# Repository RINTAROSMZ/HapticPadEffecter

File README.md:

# HapticPadEffecter
触感再現技術による音響効果フィードバックを備えたトラックパッド式エフェクター

Capative PCB trackpad (diamond pattern)

Intuitive manipulation of the parameters of Distortion and Spatial effects

Touch IC:MTCH6102

Haptic:DRV2605L+LRA

DigiPot:MCP42010

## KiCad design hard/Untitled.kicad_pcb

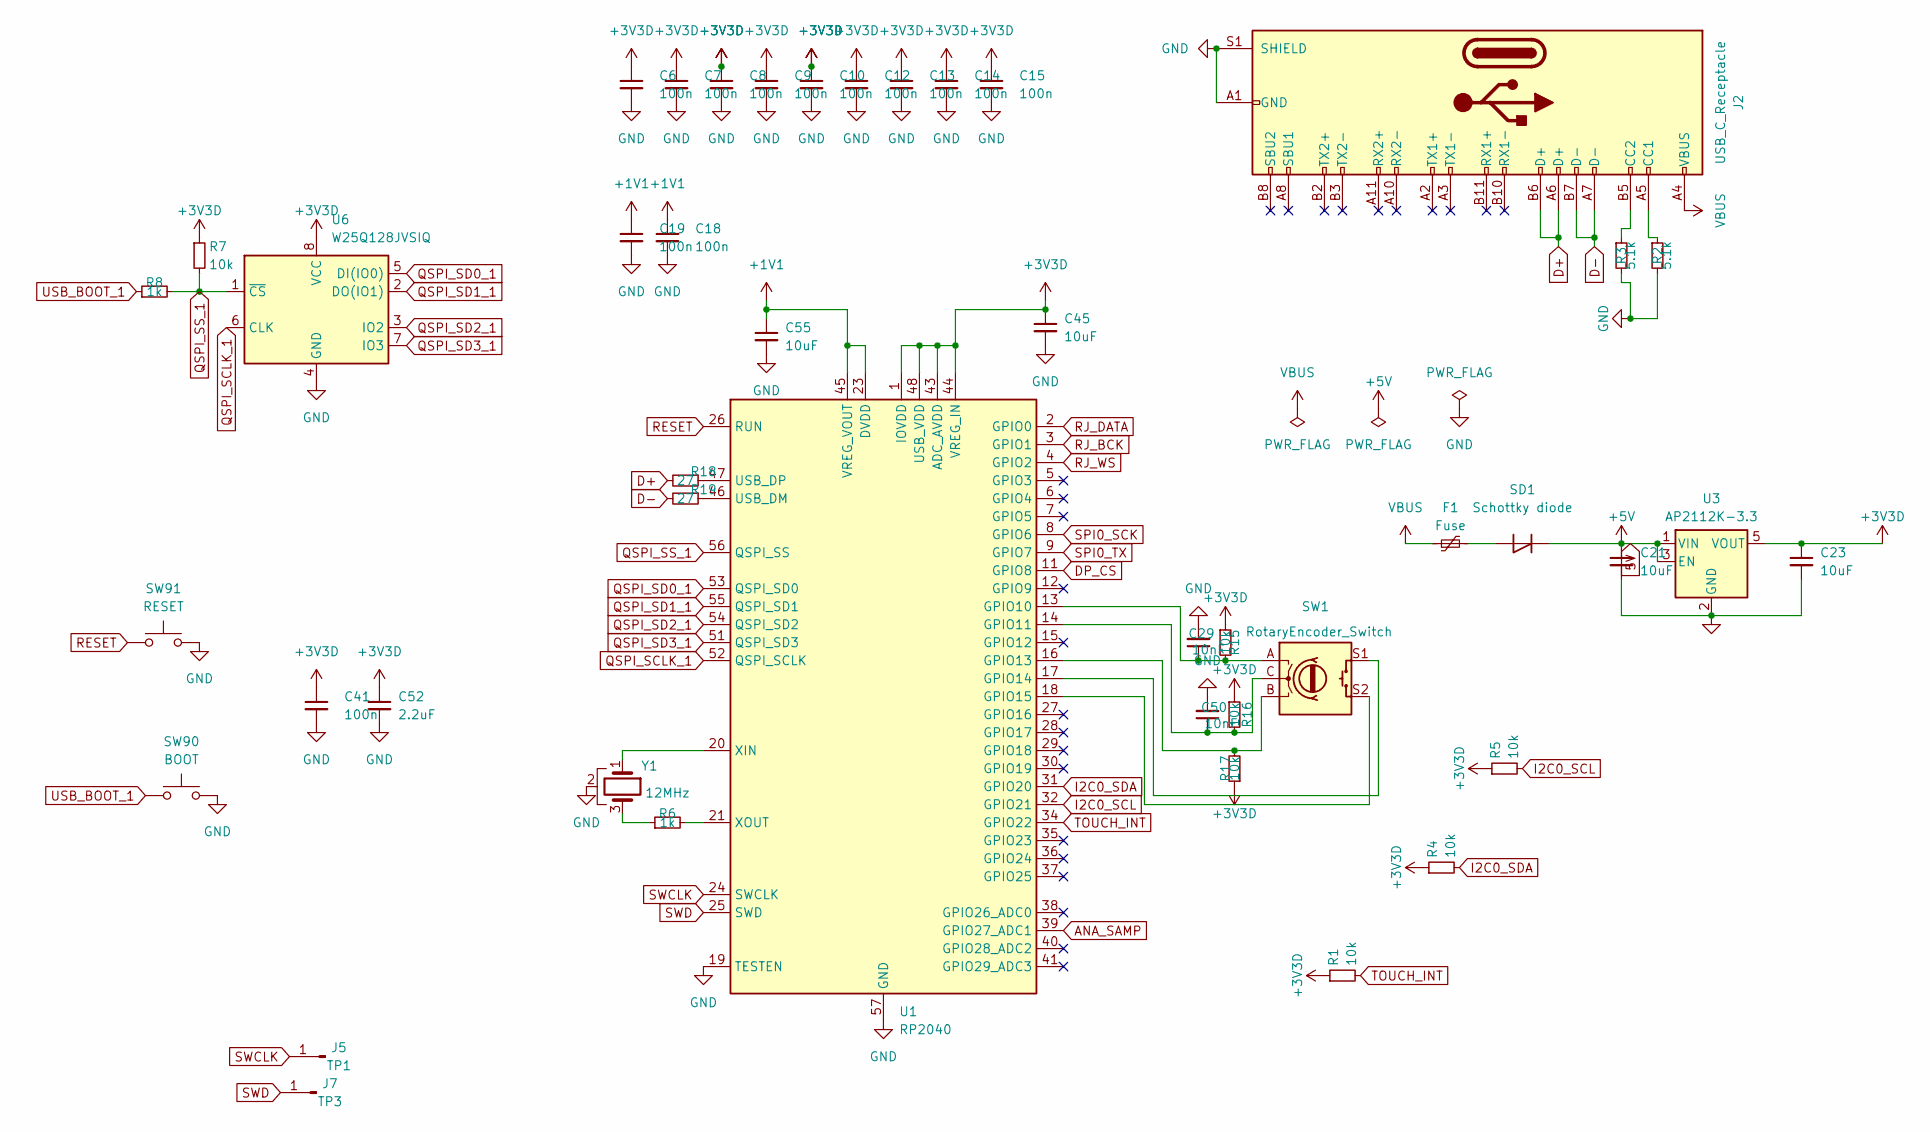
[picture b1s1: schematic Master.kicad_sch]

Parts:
C6, C7, C8, C9, C10, C12, C13, C14, C15, C18, C19, C41: 100n; C_0402_1005Metric; LCSC C1525
C21, C23, C45, C55: 10uF; C_1206_3216Metric; LCSC C13585
C29, C50: 10nF; C_0805_2012Metric; LCSC C1710
C52: 2.2uF; C_1206_3216Metric; LCSC C50254
F1: Fuse; Fuse_0603_1608Metric; LCSC C187605
J2: USB_C_Receptacle; USB_C_Receptacle_HRO_TYPE-C-31-M-12; LCSC C165948
J5: TP1; TestPoint_Pad_D1.0mm
J7: TP3; TestPoint_Pad_D1.0mm
R1, R4, R5, R7, R15, R16, R17: 10k; R_0402_1005Metric; LCSC C25744
R2, R3: 5.1k; R_0402_1005Metric; LCSC C25905
R6, R8: 1k; R_0402_1005Metric; LCSC C11702
R18, R19: 27; R_0402_1005Metric; LCSC C25100
SD1: Schottky diode; D_SOD-123; LCSC C8598
SW1: RotaryEncoder_Switch; RotaryEncoder_Bourns_Vertical_PEC12R-3x17F-Sxxxx
SW90: BOOT; SW_SPST_PTS810; LCSC C92589
SW91: RESET; SW_SPST_PTS810; LCSC C92589
U1: RP2040; QFN-56-1EP_7x7mm_P0.4mm_EP3.2x3.2mm; LCSC C2040
U3: AP2112K-3.3; SOT-23-5; LCSC C51118
U6: W25Q128JVSIQ; SOIC-8_5.3x5.3mm_P1.27mm; LCSC C97521
Y1: 12MHz; Resonator_SMD_Murata_CSTxExxV-3Pin_3.0x1.1mm; LCSC C341520

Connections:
5V: C21.1, SD1.1 (K), U3.1 (VIN), U3.3 (EN); also elsewhere on the board
+1V1: C18.1, C19.1, C55.1, U1.23 (DVDD), U1.45 (VREG_VOUT), U1.50 (DVDD)
+3V3D: C6.1, C7.1, C8.1, C9.1, C10.1, C12.1, C13.1, C14.1, C15.1, C23.1, C41.1, C45.1, C52.1, R1.1, R4.1, R5.1, R7.1, R15.1, R16.1, R17.1, U1.1 (IOVDD), U1.10 (IOVDD), U1.22 (IOVDD), U1.33 (IOVDD), U1.42 (IOVDD), U1.43 (ADC_AVDD), U1.44 (VREG_IN), U1.48 (USB_VDD), U1.49 (IOVDD), U3.5 (VOUT), U6.8 (VCC); also elsewhere on the board
ANA_SAMP: U1.39 (GPIO27_ADC1)
D+: J2.A6 (D+), J2.B6 (D+), R18.2
D-: J2.A7 (D-), J2.B7 (D-), R19.2
DP_CS: U1.11 (GPIO8); also elsewhere on the board
GND: C6.2, C7.2, C8.2, C9.2, C10.2, C12.2, C13.2, C14.2, C15.2, C18.2, C19.2, C21.2, C23.2, C29.2, C41.2, C45.2, C50.2, C52.2, C55.2, J2.A1 (GND), J2.A12 (GND), J2.B1 (GND), J2.B12 (GND), J2.S1 (SHIELD), R2.2, R3.2, SW90.2, SW91.2, U1.19 (TESTEN), U1.57 (GND), U3.2 (GND), U6.4 (GND), Y1.2; also elsewhere on the board
I2C0_SCL: R5.2, U1.32 (GPIO21); also elsewhere on the board
I2C0_SDA: R4.2, U1.31 (GPIO20); also elsewhere on the board
unnamed: J2.A5 (CC1), R2.1
unnamed: J2.B5 (CC2), R3.1
unnamed: R6.1, Y1.3
unnamed: F1.2, SD1.2 (A)
unnamed: C29.1, R15.2, SW1.A, U1.13 (GPIO10)
unnamed: C50.1, R16.2, SW1.C, U1.14 (GPIO11)
unnamed: R17.2, SW1.B, U1.16 (GPIO13)
unnamed: SW1.S1, U1.17 (GPIO14)
unnamed: SW1.S2, U1.18 (GPIO15)
unnamed: R19.1, U1.46 (USB_DM)
unnamed: R18.1, U1.47 (USB_DP)
unnamed: U1.20 (XIN), Y1.1
unnamed: R6.2, U1.21 (XOUT)
QSPI_SCLK_1: U1.52 (QSPI_SCLK), U6.6 (CLK)
QSPI_SD0_1: U1.53 (QSPI_SD0), U6.5 (DI(IO0))
QSPI_SD1_1: U1.55 (QSPI_SD1), U6.2 (DO(IO1))
QSPI_SD2_1: U1.54 (QSPI_SD2), U6.3 (IO2)
QSPI_SD3_1: U1.51 (QSPI_SD3), U6.7 (IO3)
QSPI_SS_1: R7.2, R8.2, U1.56 (QSPI_SS), U6.1 (~CS)
RESET: SW91.1, U1.26 (RUN)
RJ_BCK: U1.3 (GPIO1); also elsewhere on the board
RJ_DATA: U1.2 (GPIO0); also elsewhere on the board
RJ_WS: U1.4 (GPIO2); also elsewhere on the board
SPI0_SCK: U1.8 (GPIO6); also elsewhere on the board
SPI0_TX: U1.9 (GPIO7); also elsewhere on the board
SWCLK: J5.1, U1.24 (SWCLK)
SWD: J7.1, U1.25 (SWD)
TOUCH_INT: R1.2, U1.34 (GPIO22); also elsewhere on the board
USB_BOOT_1: R8.1, SW90.1
VBUS: F1.1, J2.A4 (VBUS), J2.A9 (VBUS), J2.B4 (VBUS), J2.B9 (VBUS); also elsewhere on the board

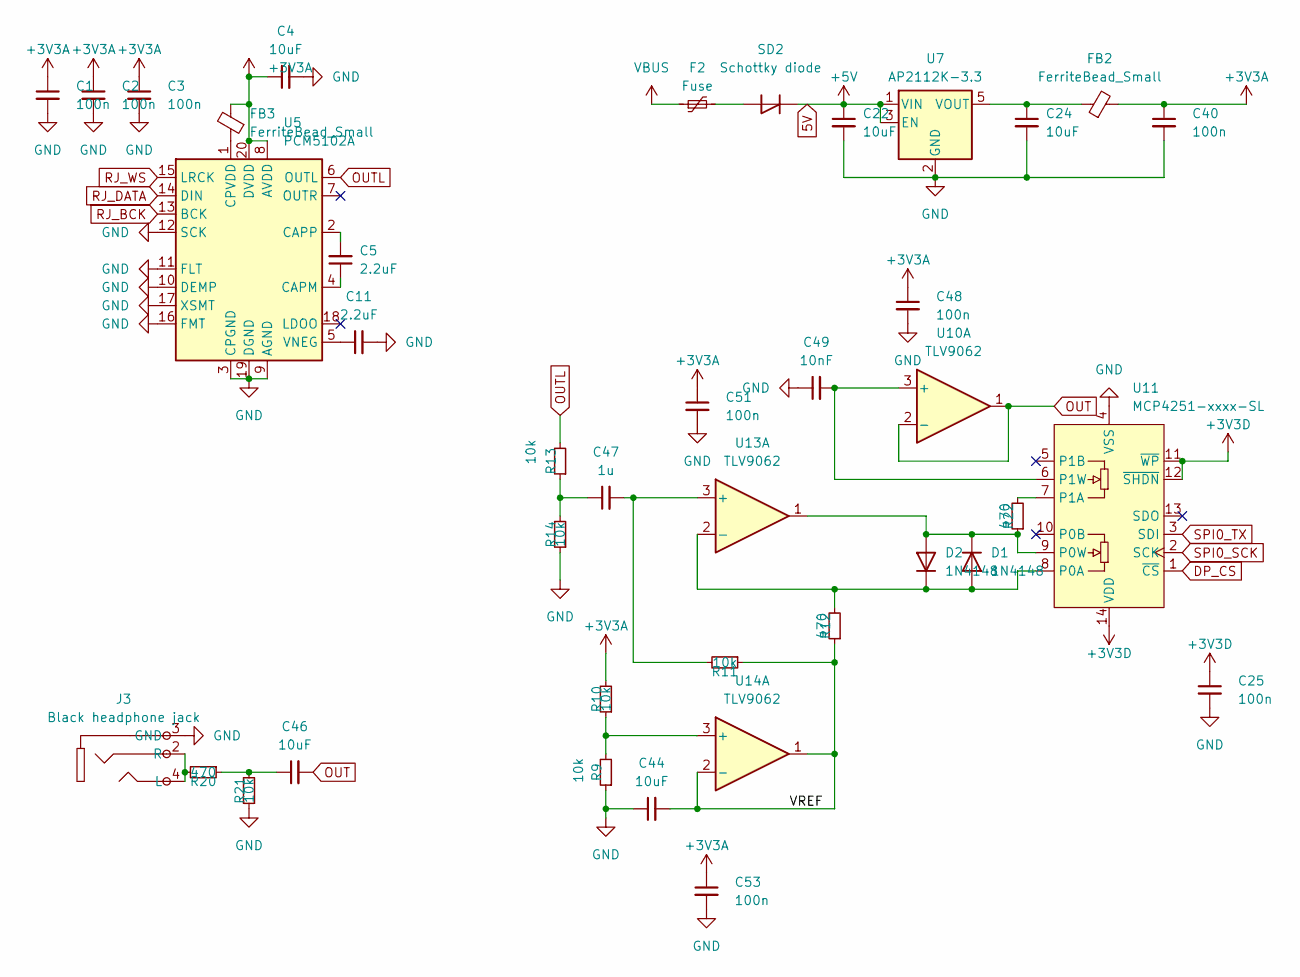
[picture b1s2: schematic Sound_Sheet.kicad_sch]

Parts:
C1, C2, C3, C25, C40, C48, C51, C53: 100n; C_0402_1005Metric; LCSC C1525
C4, C22, C24, C44, C46: 10uF; C_1206_3216Metric; LCSC C13585
C5, C11: 2.2uF; C_1206_3216Metric; LCSC C50254
C47: 1u; C_0603_1608Metric; LCSC C15849
C49: 10nF; C_0805_2012Metric; LCSC C1710
D1, D2: 1N4148; D_SOD-323; LCSC C2128
F2: Fuse; Fuse_0603_1608Metric; LCSC C187605
FB2, FB3: FerriteBead_Small; L_0603_1608Metric; LCSC C1002
J3: Black headphone jack; AUDIO-TH_320B; LCSC Part C18166
R9, R10, R11, R13, R14, R21: 10k; R_0402_1005Metric; LCSC C25744
R12, R20, R22: 470; R_0805_2012Metric; LCSC C17710
SD2: Schottky diode; D_SOD-123; LCSC C8598
U5: PCM5102A; TSSOP-20_4.4x6.5mm_P0.65mm; LCSC C107671
U7: AP2112K-3.3; SOT-23-5; LCSC C51118
U10, U13, U14: TLV9062; SOIC-8_L5.0-W4.0-P1.27-LS6.0-BL; LCSC C398355
U11: MCP4251-xxxx-SL; SOIC-14_3.9x8.7mm_P1.27mm; LCSC C640896

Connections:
5V: C22.1, SD2.1 (K), U7.1 (VIN), U7.3 (EN); also elsewhere on the board
+3V3A: C1.1, C2.1, C3.1, C4.1, C40.1, C48.1, C51.1, C53.1, FB2.2, FB3.2, R10.2, U5.8 (AVDD), U5.20 (DVDD), U10.8 (V+), U13.8 (V+), U14.8 (V+)
+3V3D: C25.1, U11.11 (~WP), U11.12 (~SHDN), U11.14 (VDD); also elsewhere on the board
/Sound_Sheet/VREF: C44.2, R11.1, R12.1, U14.1, U14.2 (-)
DP_CS: U11.1 (~CS); also elsewhere on the board
GND: C1.2, C2.2, C3.2, C4.2, C11.2, C22.2, C24.2, C25.2, C40.2, C44.1, C48.2, C49.1, C51.2, C53.2, J3.3 (GND), R9.1, R14.1, R21.1, U5.3 (CPGND), U5.9 (AGND), U5.10 (DEMP), U5.11 (FLT), U5.12 (SCK), U5.16 (FMT), U5.17 (XSMT), U5.19 (DGND), U7.2 (GND), U10.4 (V-), U11.4 (VSS), U13.4 (V-), U14.4 (V-); also elsewhere on the board
unnamed: C46.1, R20.1, R21.2
unnamed: C47.1, R13.1, R14.2
unnamed: D1.2 (A), D2.1 (K), R12.2, U11.8 (P0A), U13.2 (-)
unnamed: D1.1 (K), D2.2 (A), R22.1, U11.9 (P0W), U13.1
unnamed: J3.2 (R), J3.4 (L), R20.2
unnamed: F2.2, SD2.2 (A)
unnamed: C5.1, U5.4 (CAPM)
unnamed: C5.2, U5.2 (CAPP)
unnamed: FB3.1, U5.1 (CPVDD)
unnamed: C11.1, U5.5 (VNEG)
unnamed: C24.1, FB2.1, U7.5 (VOUT)
unnamed: C49.2, U10.3 (+), U11.6 (P1W)
unnamed: R22.2, U11.7 (P1A)
unnamed: C47.2, R11.2, U13.3 (+)
unnamed: R9.2, R10.1, U14.3 (+)
OUT: C46.2, U10.1, U10.2 (-)
OUTL: R13.2, U5.6 (OUTL)
RJ_BCK: U5.13 (BCK); also elsewhere on the board
RJ_DATA: U5.14 (DIN); also elsewhere on the board
RJ_WS: U5.15 (LRCK); also elsewhere on the board
SPI0_SCK: U11.2 (SCK); also elsewhere on the board
SPI0_TX: U11.3 (SDI); also elsewhere on the board
VBUS: F2.1; also elsewhere on the board

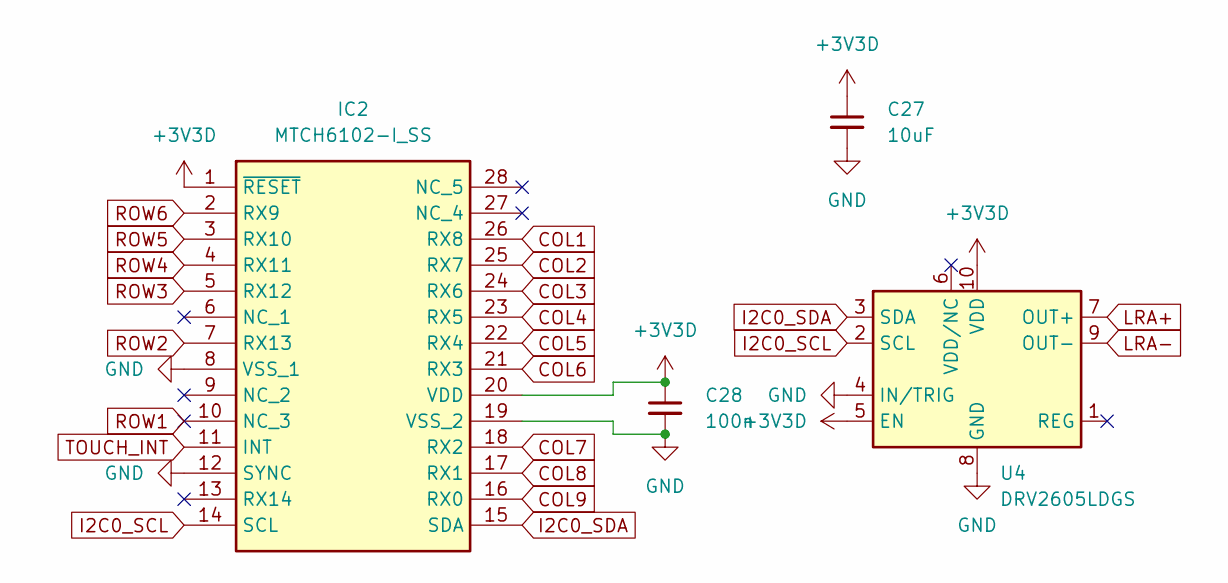
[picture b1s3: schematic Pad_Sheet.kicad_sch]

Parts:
C27: 10uF; C_1206_3216Metric; LCSC C13585
C28: 100n; C_0402_1005Metric; LCSC C1525
IC2: MTCH6102-I_SS; SSOP-28_L10.2-W5.3-P0.65-LS7.8-BL; Manufacturer_Part_Number MTCH6102-I/SS; Mouser Part Number 579-MTCH6102-I/SS
U4: DRV2605LDGS; VSSOP-10_3x3mm_P0.5mm; LCSC C527464

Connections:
+3V3D: C27.1, C28.1, IC2.1 (~RESET), IC2.20 (VDD), U4.5 (EN), U4.10 (VDD); also elsewhere on the board
COL1: IC2.26 (RX8)
COL2: IC2.25 (RX7)
COL3: IC2.24 (RX6)
COL4: IC2.23 (RX5)
COL5: IC2.22 (RX4)
COL6: IC2.21 (RX3)
COL7: IC2.18 (RX2)
COL8: IC2.17 (RX1)
COL9: IC2.16 (RX0)
GND: C27.2, C28.2, IC2.8 (VSS_1), IC2.12 (SYNC), IC2.19 (VSS_2), U4.4 (IN/TRIG), U4.8 (GND); also elsewhere on the board
I2C0_SCL: IC2.14 (SCL), U4.2 (SCL); also elsewhere on the board
I2C0_SDA: IC2.15 (SDA), U4.3 (SDA); also elsewhere on the board
LRA+: U4.7 (OUT+)
LRA-: U4.9 (OUT-)
ROW1: IC2.10 (NC_3)
ROW2: IC2.7 (RX13)
ROW3: IC2.5 (RX12)
ROW4: IC2.4 (RX11)
ROW5: IC2.3 (RX10)
ROW6: IC2.2 (RX9)
TOUCH_INT: IC2.11 (INT); also elsewhere on the board

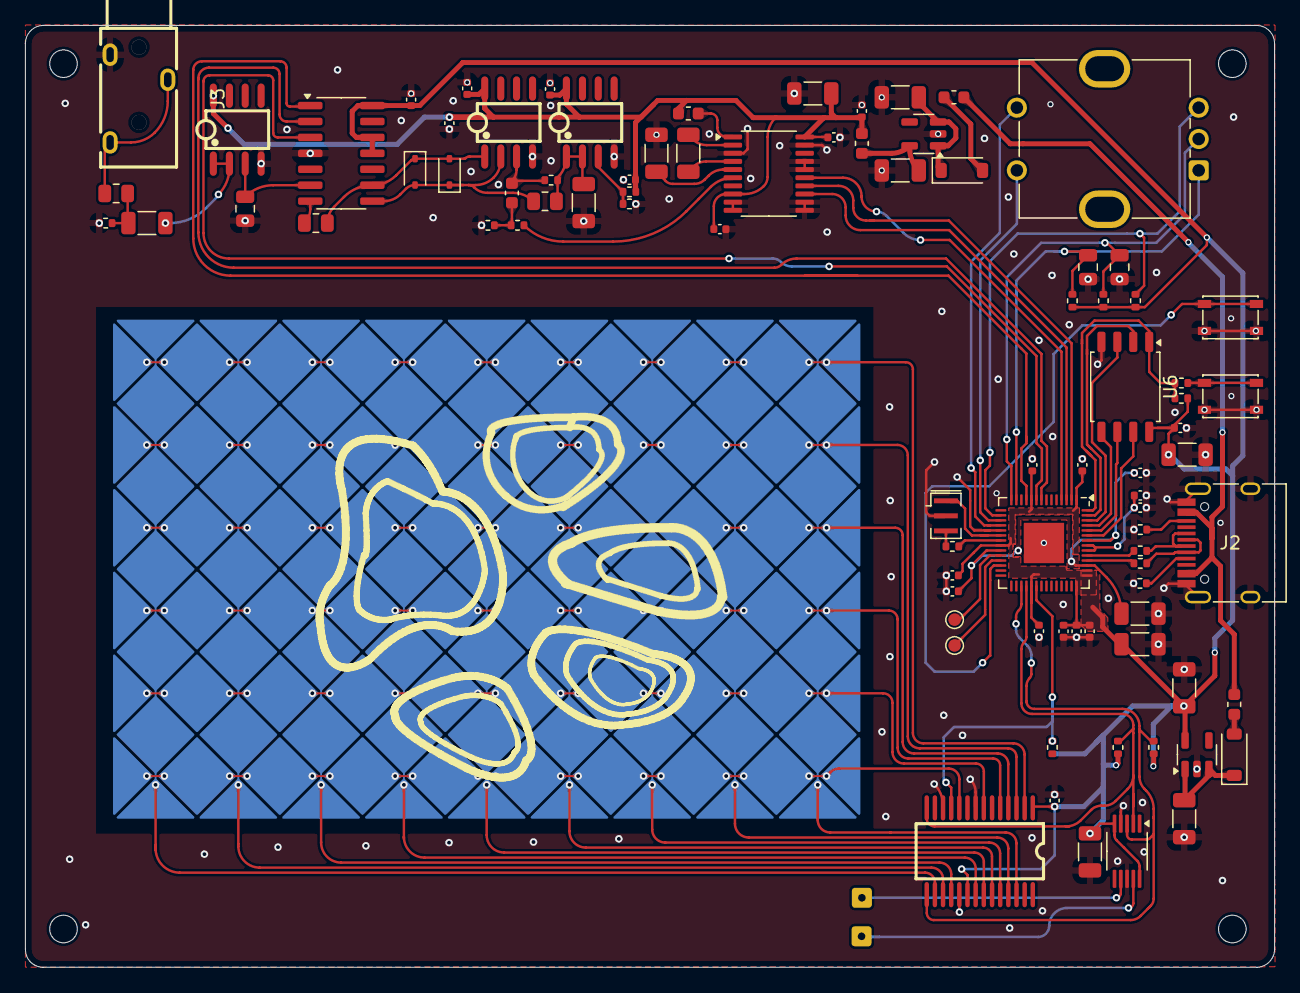
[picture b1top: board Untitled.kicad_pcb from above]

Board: 2 copper layers, 99.6 x 75.1 mm, 87 parts (0 on the bottom side), 58 nets.

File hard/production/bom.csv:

Designator,Footprint,Quantity,Value,LCSC Part #
"C1, C10, C12, C13, C14, C15, C18, C19, C2, C25, C28, C3, C40, C41, C48, C51, C53, C6, C7, C8, C9",0402,21,100n,C1525
"C11, C5, C52",1206,3,2.2uF,C50254
"C21, C22, C23, C24, C27, C4, C44, C45, C46, C55",1206,10,10uF,C13585
"C29, C49, C50",0805,3,10nF,C1710
C47,0603,1,1u,C15849
"D1, D2",D_SOD-323,2,1N4148,C2128
"F1, F2",0603,2,Fuse,C187605
"FB2, FB3",0603,2,FerriteBead_Small,C1002
IC2,SSOP-28_L10.2-W5.3-P0.65-LS7.8-BL,1,MTCH6102-I_SS,C641630
J2,USB_C_Receptacle_HRO_TYPE-C-31-M-12,1,USB_C_Receptacle,C165948
J3,AUDIO-TH_320B,1,Black headphone jack,C18166
J5,TestPoint_Pad_D1.0mm,1,TP1,
J7,TestPoint_Pad_D1.0mm,1,TP3,
"R1, R10, R11, R13, R14, R15, R16, R17, R21, R4, R5, R7, R9",0402,13,10k,C25744
"R12, R20, R22",0805,3,470,C17710
"R18, R19",0402,2,27,C25100
"R2, R3",0402,2,5.1k,C25905
"R6, R8",0402,2,1k,C11702
"SD1, SD2",D_SOD-123,2,Schottky diode,C8598
SW1,RotaryEncoder_Bourns_Vertical_PEC12R-3x17F-Sxxxx,1,RotaryEncoder_Switch,
SW90,SW_SPST_PTS810,1,BOOT,C92589
SW91,SW_SPST_PTS810,1,RESET,C92589
U1,QFN-56-1EP_7x7mm_P0.4mm_EP3.2x3.2mm,1,RP2040,C2040
"U10, U13, U14",SOIC-8_L5.0-W4.0-P1.27-LS6.0-BL,3,TLV9062,C398355
U11,SOIC-14_3.9x8.7mm_P1.27mm,1,MCP4251-xxxx-SL,C640896
"U3, U7",SOT-23-5,2,AP2112K-3.3,C51118
U4,VSSOP-10_3x3mm_P0.5mm,1,DRV2605LDGS,C527464
U5,TSSOP-20_4.4x6.5mm_P0.65mm,1,PCM5102A,C107671
U6,SOIC-8_5.3x5.3mm_P1.27mm,1,W25Q128JVSIQ,C97521
Y1,Resonator_SMD_Murata_CSTxExxV-3Pin_3.0x1.1mm,1,12MHz,C341520

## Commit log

2026-03-29 Uploading_Kicad_and_gerber_file
2026-03-29 uploading_Kicad_and_Gerber_files
2026-03-29 Ignore KiCad backup files and remove them from index
2026-03-29 Fixing typo and remove config files
2026-03-29 Fixed typo
2026-03-29 Removed config files
2026-03-29 added parts selection
2026-03-29 Modifying paths
2026-03-29 upload gerber file
2026-03-29 fixed DRC errors
2026-03-29 fixed position of jack
2026-04-09 fixed pad errors
